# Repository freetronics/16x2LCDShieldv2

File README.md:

Freetronics 16x2 LCD Shield
===========================
Copyright 2011 Freetronics Pty Ltd  
Freetronics site:  <www.freetronics.com>  
Freetronics email: <info@freetronics.com>  

A compact shield to connect an HD44780-compatible, 16x2 LCD module
and interface buttons to an Arduino or compatible such as a
Freetronics Eleven.

Features:

 * Reset button connected to Arduino reset pin.
 * 100nF smoothing capacitor.
 * Buttons for "up", "down", "left", "right", and "select" all on a
   single analog input pin.
 * Parts overlay on both the top and the bottom.

More information is available at:

  http://www.freetronics.com/16x2lcd

The "docs" folder within this repository includes a handy copy of the
schematic in PDF format and image(s) of the pcb.

INSTALLATION
------------
The design is saved as an EAGLE project. EAGLE PCB design software is
available from www.cadsoftusa.com free for non-commercial use. To use
this project download it and place the directory containing these files
into the "eagle" directory on your computer. Then open EAGLE and
navigate to Projects -> eagle -> 16x2LCDShieldv2.

DISTRIBUTION
------------
The specific terms of distribution of this project are governed by the
license referenced below.

LICENSE
-------
Licensed under the TAPR Open Hardware License (www.tapr.org/OHL).
The "license" folder within this repository also contains a copy of
this license in plain text format.

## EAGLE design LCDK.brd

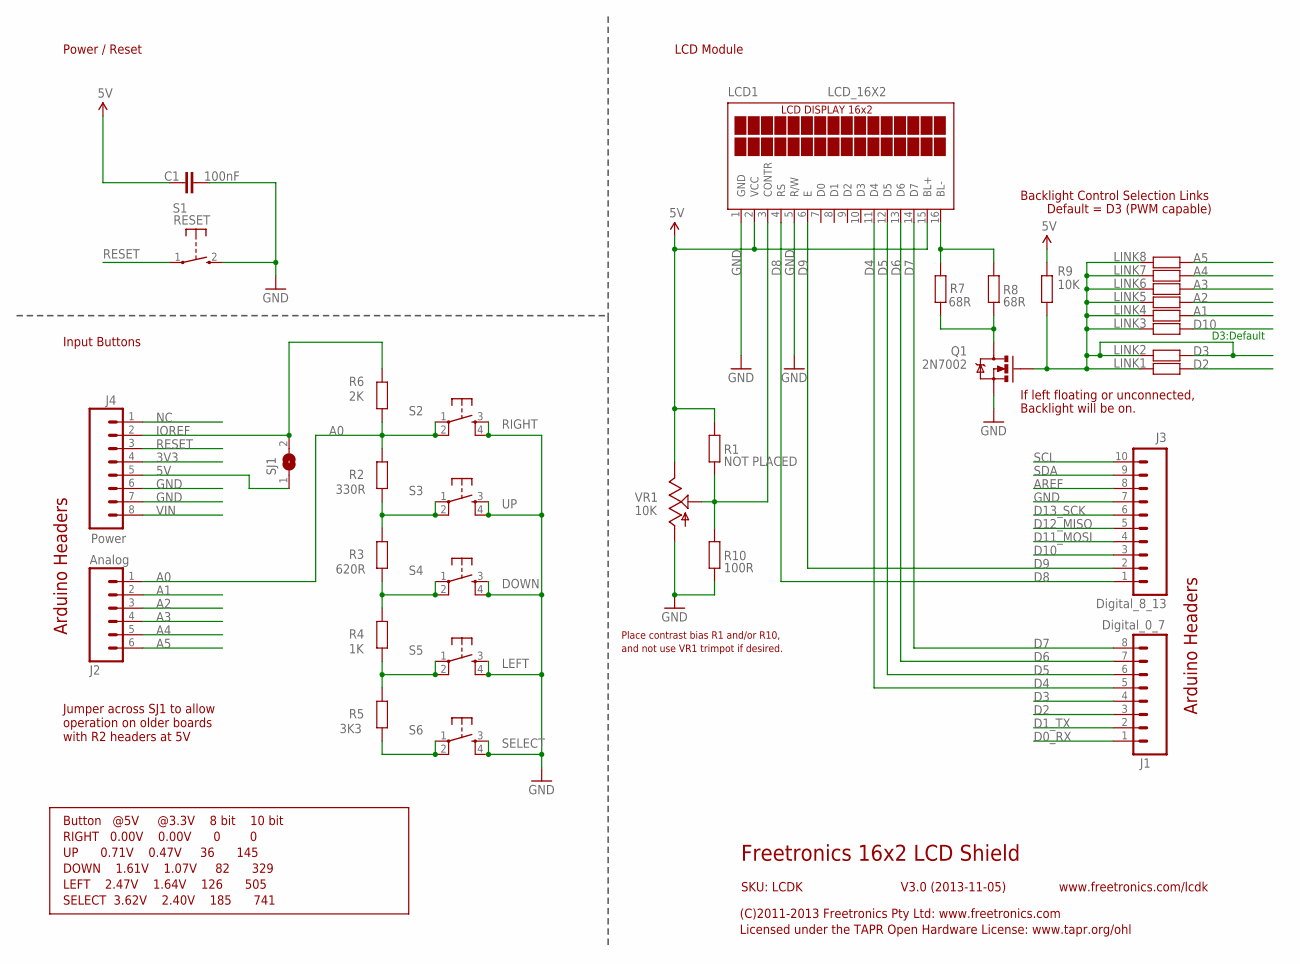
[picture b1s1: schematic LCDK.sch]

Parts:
C1: 100nF; 0603
J1: Digital_0_7; 1X08
J2: Analog; 1X06
J3: Digital_8_13; 1X10
J4: Power; 1X08
LCD1: LCD_16X2; LCD_16X2_REAR
LINK1, LINK2, LINK3, LINK4, LINK5, LINK6, LINK7, LINK8: RESISTOR0603; 0603
Q1: 2N7002; SOT23-3
R1: NOT PLACED; 0603
R2: 330R; 0603
R3: 620R; 0603
R4: 1K; 0603
R5: 3K3; 0603
R6: 2K; 0603
R7, R8: 68R; 0603
R9: 10K; 0603
R10: 100R; 0603
S1: RESET; TACTILE_SWITCH_SMD_2PIN_TINY
S2: RIGHT; TACTILE-PTH-4.5MM
S3: UP; TACTILE-PTH-4.5MM
S4: DOWN; TACTILE-PTH-4.5MM
S5: LEFT; TACTILE-PTH-4.5MM
S6: SELECT; TACTILE-PTH-4.5MM
SJ1: SJN; SJ
VR1: 10K; RTRIM3314J

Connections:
3V3: J4.4
5V: C1.1, J4.5, LCD1.2 (VCC), LCD1.15 (BL+), R1.2, R9.1, SJ1.1, VR1.2 (E)
A0: J2.1, R2.2, R6.1, S2.1, S2.2
A1: J2.2, LINK4.1
A2: J2.3, LINK5.1
A3: J2.4, LINK6.1
A4: J2.5, LINK7.1
A5: J2.6, LINK8.1
AREF: J3.8
D0_RX: J1.1
D1_TX: J1.2
D2: J1.3, LINK1.1
D3: J1.4, LINK1.2, LINK2.1, LINK2.2, LINK3.2, LINK4.2, LINK5.2, LINK6.2, LINK7.2, LINK8.2, Q1.1 (G), R9.2
D4: J1.5, LCD1.11 (D4)
D5: J1.6, LCD1.12 (D5)
D6: J1.7, LCD1.13 (D6)
D7: J1.8, LCD1.14 (D7)
D8: J3.1, LCD1.4 (RS)
D9: J3.2, LCD1.6 (E)
D10: J3.3, LINK3.1
D11_MOSI: J3.4
D12_MISO: J3.5
D13_SCK: J3.6
GND: C1.2, J3.7, J4.6, J4.7, LCD1.1 (GND), LCD1.5 (R/W), Q1.2 (S), R10.1, S1.2 (S), S2.3, S2.4, S3.3, S3.4, S4.3, S4.4, S5.3, S5.4, S6.3, S6.4, VR1.1 (A)
IOREF: J4.2, R6.2, SJ1.2
unnamed: LCD1.3 (CONTR), R1.1, R10.2, VR1.W (S)
unnamed: R5.1, S6.1, S6.2
unnamed: R4.1, R5.2, S5.1, S5.2
unnamed: LCD1.16 (BL-), R7.2, R8.2
unnamed: Q1.3 (D), R7.1, R8.1
unnamed: R3.1, R4.2, S4.1, S4.2
unnamed: R2.1, R3.2, S3.1, S3.2
NC: J4.1
RESET: J4.3, S1.1
SCL: J3.10
SDA: J3.9
VIN: J4.8

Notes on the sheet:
Freetronics 16x2 LCD Shield
V3.0 (2013-11-05)
SKU: LCDK
Arduino Headers
Power / Reset
LCD Module
Input Buttons
(C)2011-2013 Freetronics Pty Ltd: www.freetronics.com
Licensed under the TAPR Open Hardware License: www.tapr.org/ohl
www.freetronics.com/lcdk
Backlight Control Selection Links
Default = D3 (PWM capable)
D3:Default
Place contrast bias R1 and/or R10,
and not use VR1 trimpot if desired.
Button @5V @3.3V 8 bit 10 bit RIGHT 0.00V 0.00V 0 0 UP 0.71V 0.47V 36 145 DOWN 1.61V 1.07V 82 329 LEFT 2.47V 1.64V 126 505 SELECT 3.62V 2.40V 185 741
If left floating or unconnected,
Backlight will be on.
Jumper across SJ1 to allow operation on older boards with R2 headers at 5V

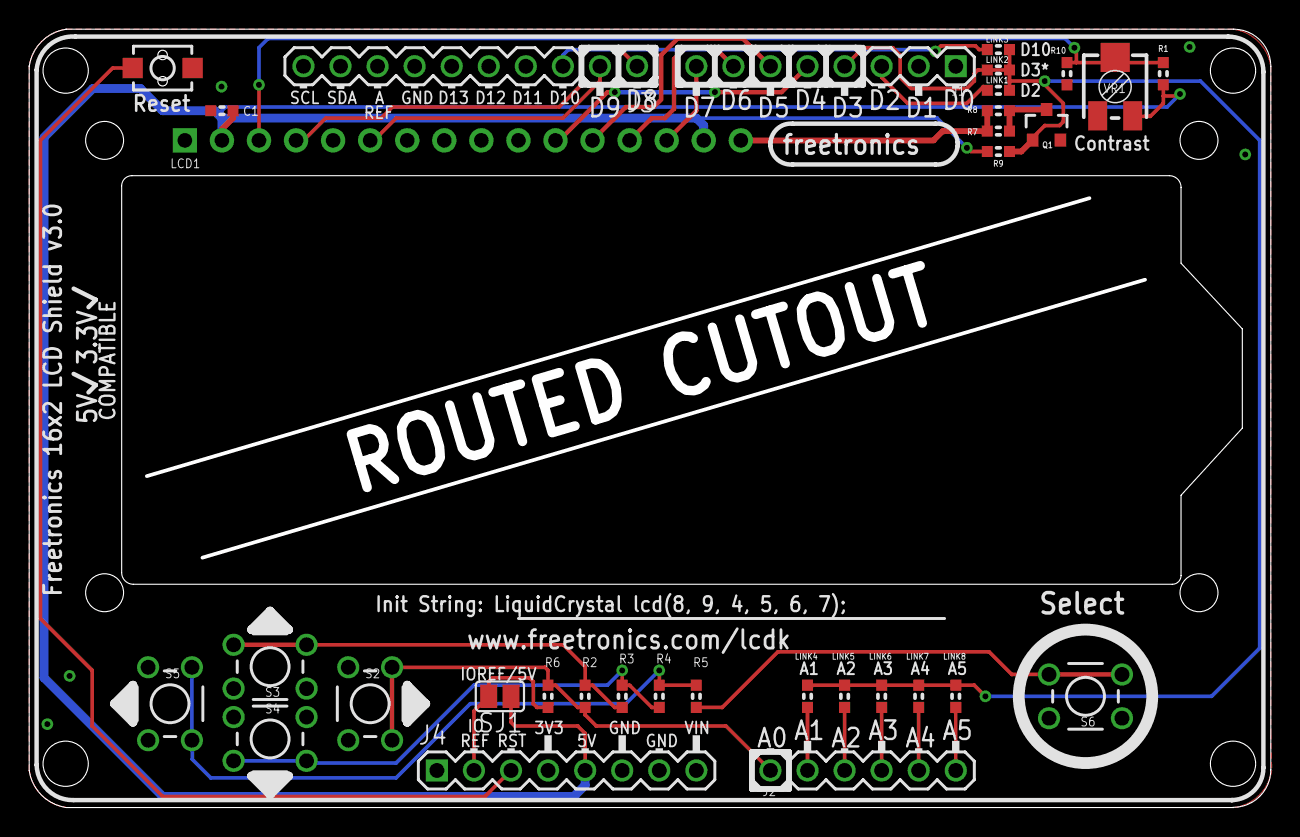
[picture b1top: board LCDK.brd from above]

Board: 2 copper layers, 84.8 x 53.1 mm, 33 parts (0 on the bottom side), 26 nets.

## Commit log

2011-03-30 Initial import of incomplete project
2011-04-10 v2 Initial setup - final choices to be made
2011-04-21 Left alignment done and checked
2011-04-28 Before final lookover and release
2011-04-29 LCD Backlight moved to D3, new smt trimpot footprint
2011-05-03 Final before release gerbers and inspection
2011-05-04 Full production
2011-05-18 Button ladder voltage and reading values fixed
2013-11-05 Converted menu buttons to through hole; renamed project files for v3.0 release
2014-06-11 Add 3.3V/5V compatible label on silkscreen
